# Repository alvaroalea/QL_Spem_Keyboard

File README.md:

# QL_Spem_Keyboard

Recreation of the mechanical keyboard for Sinclair QL computer by brand Spem

# WARNING: DO NOT USE THIS PROJECT IS NOT TESTED AND MISSING THINGS

Spem SRL, a italian company manufacture in 1986 a conversion kit for the Sinclair QL, named "System 2",
This include a aluminium desktop case with space for up to two 3 1/2" drives, the QL original Power supply and a Sinclair QL main board, to create a complete moderm desktop computer.

The case also incorporate a backplane where you can install a memory expansion and a disk interface.

The System 2 come with a full mechanical Keyboard, including numeric keys and 10 function keys, Spem use a unique aproach, and instead to provida a normal PC keyboard with a DIN-5 conector, design a specific one that connect directly to the keyboard conectors of the original Sinclair QL, and provide the aditional keys.

This is easy identificable because of the 20 cores ribbon cable the go from the keyboard to the case.

This project try to recreate this keyboard as identical as possible.
 
# Technical Details

The keyboard use keyswitch from Japanesse brand Futaba, referene MA-41 "Tombstone" because the top of the key is similar a tomb stone, with a cross emboss in the middle, while today's tipical keyswitchs the cross raise over the key.

This keyswitch has 3 legs, 2 of they are probably internally conected, to facilitate the develop of matrix keyboards using only 1 side of the PCB.

The combinations of keys need for some keys, like the F-5 F-10 that are really F1 to F5 at same time that shift keys, are from a pair of IC of type 4066, that are integrated analog swites, to power this 2 ic a small circuit drain the power from the keyboards lines itself.

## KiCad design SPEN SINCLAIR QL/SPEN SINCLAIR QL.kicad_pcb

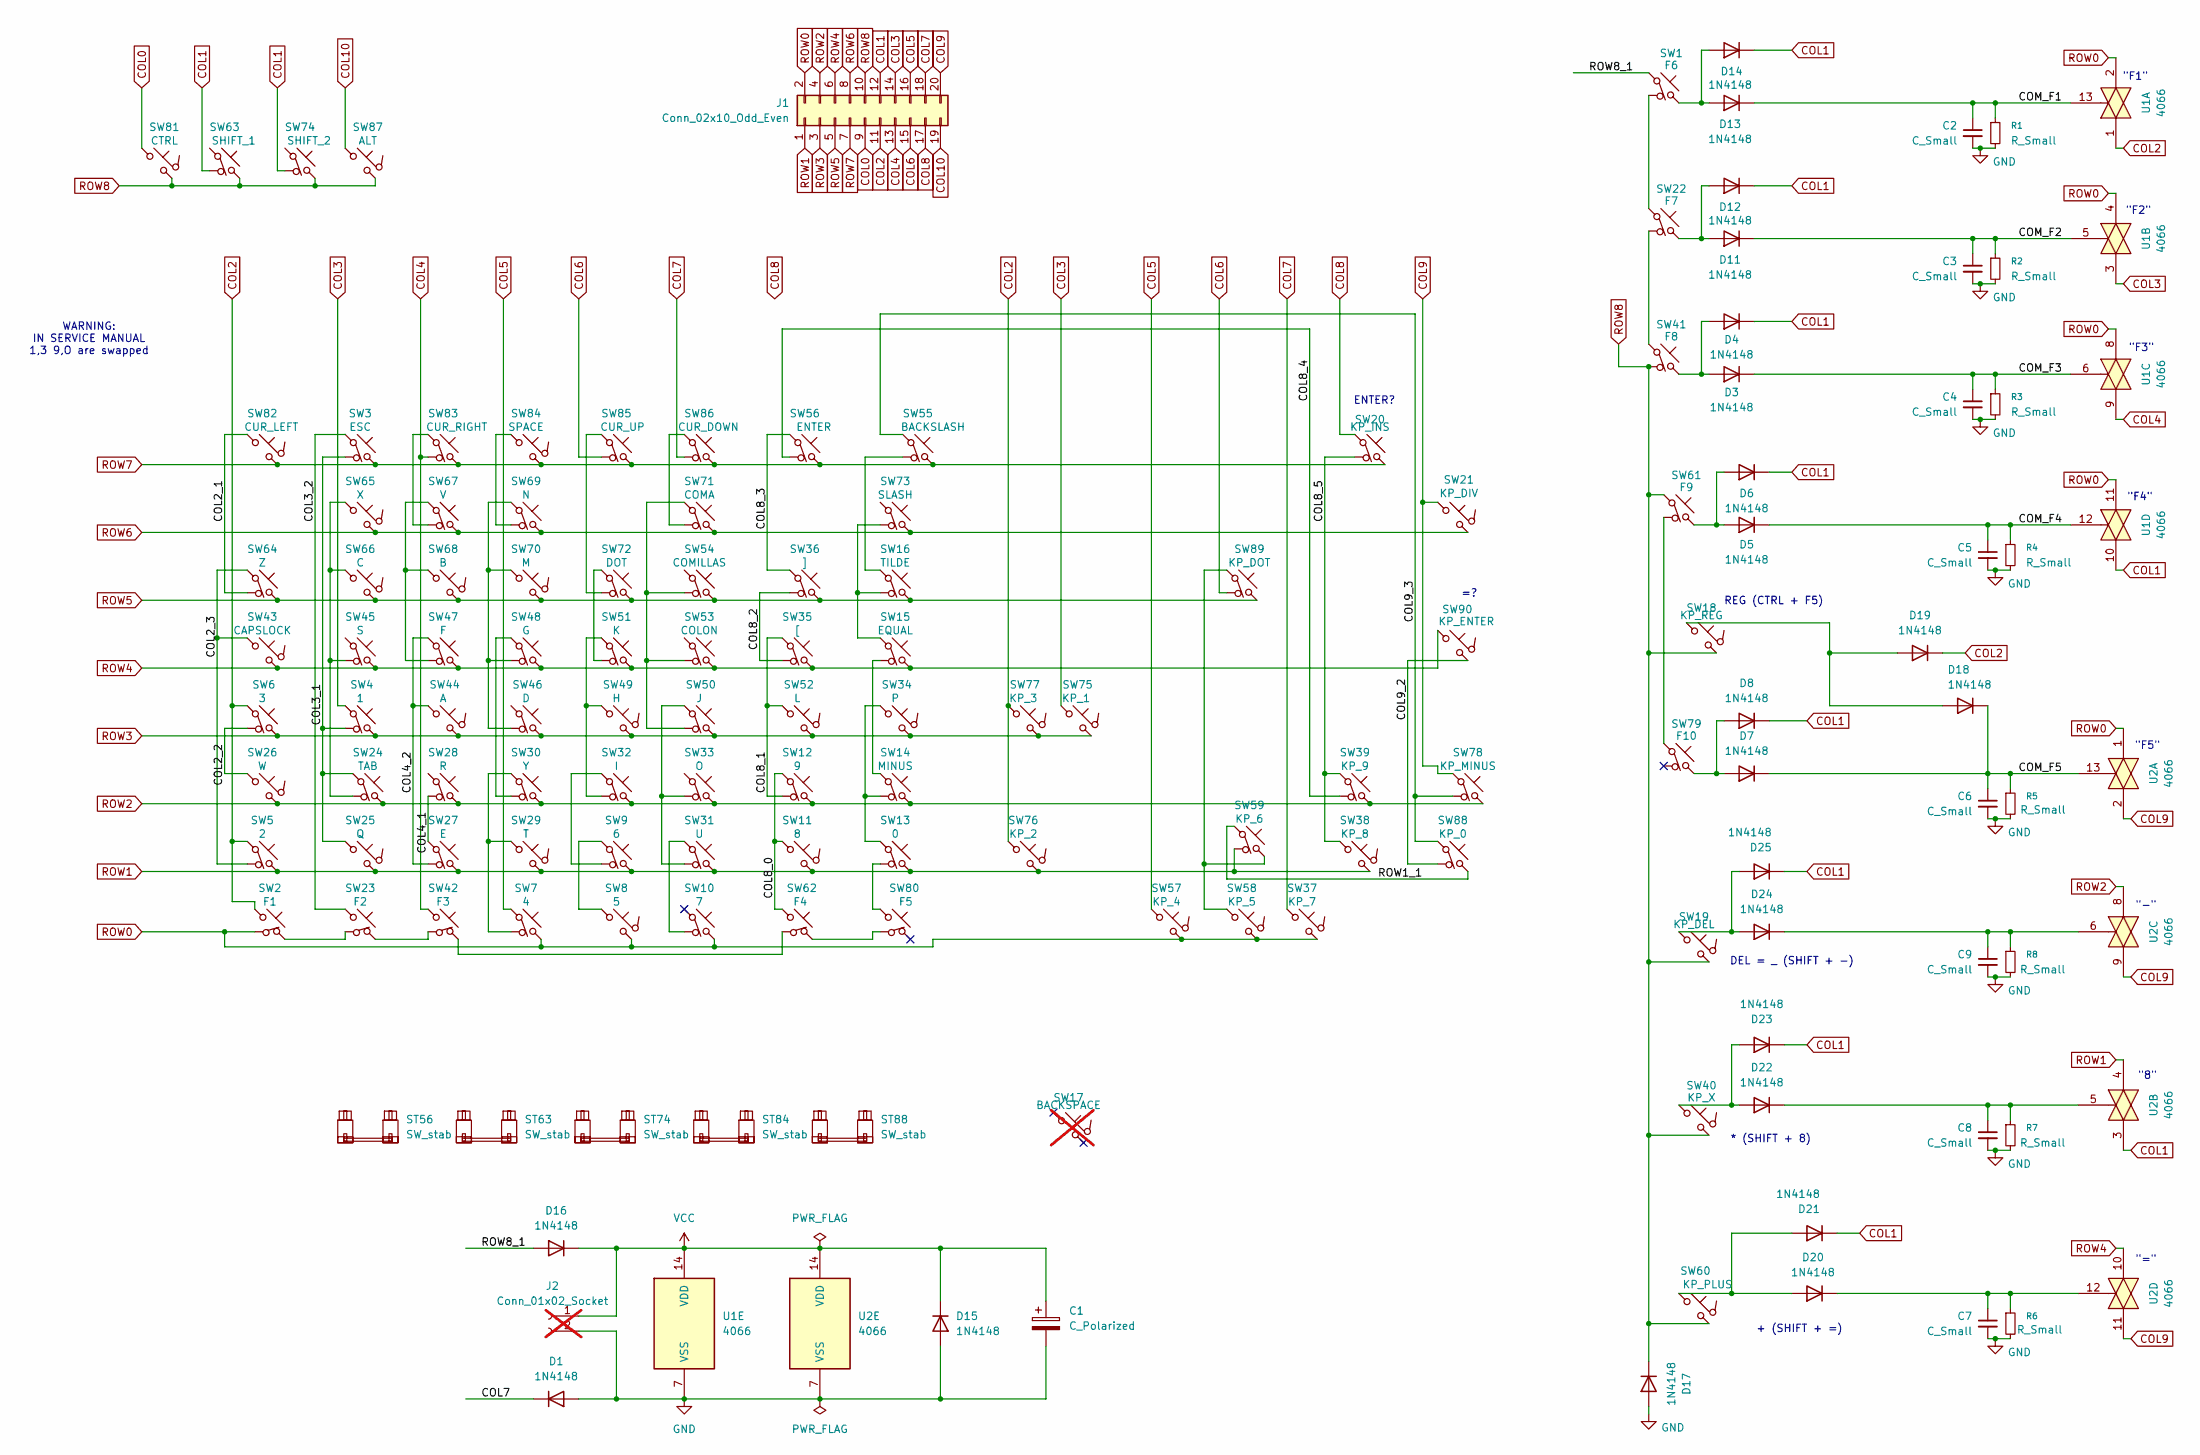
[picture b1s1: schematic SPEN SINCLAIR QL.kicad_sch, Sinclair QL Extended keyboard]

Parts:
C1: C_Polarized; C_Axial_L3.8mm_D2.6mm_P12.50mm_Horizontal
C2, C3, C4, C5, C6, C7, C8, C9: C_Small; C_Axial_DIN0207_L6.3mm_D2.5mm_P14.73mm_Horizontal
D1, D3, D4, D5, D6, D7, D8, D11, D12, D13, D14, D16, D18, D19, D20, D21, D22, D23, D24, D25: 1N4148; D_DO-35_SOD27_P10.16mm_Horizontal
D15: 1N4148; D_DO-35_SOD27_P12.70mm_Horizontal
D17: 1N4148; D_DO-35_SOD27_P7.62mm_Horizontal
J1: Conn_02x10_Odd_Even; PinHeader_2x10_P2.54mm_Horizontal
J2: Conn_01x02_Socket; PinHeader_1x02_P2.54mm_Horizontal; not fitted
R1, R2, R3, R4, R5, R6, R7, R8: R_Small; R_Axial_DIN0207_L6.3mm_D2.5mm_P14.73mm_Horizontal
ST56, ST63, ST74, ST88: SW_stab; Stabilizer_Cherry_MX_2.00u
ST84: SW_stab; Stabilizer_Cherry_MX_8.00u
SW1: F6; SW_Futaba_MA_PCB_1.00u
SW2: F1; SW_Futaba_MA_PCB_1.00u
SW3: ESC; SW_Futaba_MA_PCB_1.00u
SW4: 1; SW_Futaba_MA_PCB_1.00u
SW5: 2; SW_Futaba_MA_PCB_1.00u
SW6: 3; SW_Futaba_MA_PCB_1.00u
SW7: 4; SW_Futaba_MA_PCB_1.00u
SW8: 5; SW_Futaba_MA_PCB_1.00u
SW9: 6; SW_Futaba_MA_PCB_1.00u
SW10: 7; SW_Futaba_MA_PCB_1.00u
SW11: 8; SW_Futaba_MA_PCB_1.00u
SW12: 9; SW_Futaba_MA_PCB_1.00u
SW13: 0; SW_Futaba_MA_PCB_1.00u
SW14: MINUS; SW_Futaba_MA_PCB_1.00u
SW15: EQUAL; SW_Futaba_MA_PCB_1.00u
SW16: TILDE; SW_Futaba_MA_PCB_1.00u
SW17: BACKSPACE; SW_Futaba_MA_PCB_1.00u; not fitted
SW18: KP_REG; SW_Futaba_MA_PCB_1.00u
SW19: KP_DEL; SW_Futaba_MA_PCB_1.00u
SW20: KP_INS; SW_Futaba_MA_PCB_1.00u
SW21: KP_DIV; SW_Futaba_MA_PCB_1.00u
SW22: F7; SW_Futaba_MA_PCB_1.00u
SW23: F2; SW_Futaba_MA_PCB_1.00u
SW24: TAB; SW_Futaba_MA_PCB_1.00u
SW25: Q; SW_Futaba_MA_PCB_1.00u
SW26: W; SW_Futaba_MA_PCB_1.00u
SW27: E; SW_Futaba_MA_PCB_1.00u
SW28: R; SW_Futaba_MA_PCB_1.00u
SW29: T; SW_Futaba_MA_PCB_1.00u
SW30: Y; SW_Futaba_MA_PCB_1.00u
SW31: U; SW_Futaba_MA_PCB_1.00u
SW32: I; SW_Futaba_MA_PCB_1.00u
SW33: O; SW_Futaba_MA_PCB_1.00u
SW34: P; SW_Futaba_MA_PCB_1.00u
SW35: [; SW_Futaba_MA_PCB_1.00u
SW36: ]; SW_Futaba_MA_PCB_1.00u
SW37: KP_7; SW_Futaba_MA_PCB_1.00u
SW38: KP_8; SW_Futaba_MA_PCB_1.00u
SW39: KP_9; SW_Futaba_MA_PCB_1.00u
SW40: KP_X; SW_Futaba_MA_PCB_1.00u
SW41: F8; SW_Futaba_MA_PCB_1.00u
SW42: F3; SW_Futaba_MA_PCB_1.00u
SW43: CAPSLOCK; SW_Futaba_MA_PCB_1.00u
SW44: A; SW_Futaba_MA_PCB_1.00u
SW45: S; SW_Futaba_MA_PCB_1.00u
SW46: D; SW_Futaba_MA_PCB_1.00u
SW47: F; SW_Futaba_MA_PCB_1.00u
SW48: G; SW_Futaba_MA_PCB_1.00u
SW49: H; SW_Futaba_MA_PCB_1.00u
SW50: J; SW_Futaba_MA_PCB_1.00u
SW51: K; SW_Futaba_MA_PCB_1.00u
SW52: L; SW_Futaba_MA_PCB_1.00u
SW53: COLON; SW_Futaba_MA_PCB_1.00u
SW54: COMILLAS; SW_Futaba_MA_PCB_1.00u
SW55: BACKSLASH; SW_Futaba_MA_PCB_1.00u
SW56: ENTER; SW_Futaba_MA_PCB_1.00u
SW57: KP_4; SW_Futaba_MA_PCB_1.00u
SW58: KP_5; SW_Futaba_MA_PCB_1.00u
SW59: KP_6; SW_Futaba_MA_PCB_1.00u
SW60: KP_PLUS; SW_Futaba_MA_PCB_1.00u
SW61: F9; SW_Futaba_MA_PCB_1.00u
SW62: F4; SW_Futaba_MA_PCB_1.00u
SW63: SHIFT_1; SW_Futaba_MA_PCB_1.00u
SW64: Z; SW_Futaba_MA_PCB_1.00u
SW65: X; SW_Futaba_MA_PCB_1.00u
SW66: C; SW_Futaba_MA_PCB_1.00u
SW67: V; SW_Futaba_MA_PCB_1.00u
SW68: B; SW_Futaba_MA_PCB_1.00u
SW69: N; SW_Futaba_MA_PCB_1.00u
SW70: M; SW_Futaba_MA_PCB_1.00u
SW71: COMA; SW_Futaba_MA_PCB_1.00u
SW72: DOT; SW_Futaba_MA_PCB_1.00u
SW73: SLASH; SW_Futaba_MA_PCB_1.00u
SW74: SHIFT_2; SW_Futaba_MA_PCB_1.00u
SW75: KP_1; SW_Futaba_MA_PCB_1.00u
SW76: KP_2; SW_Futaba_MA_PCB_1.00u
SW77: KP_3; SW_Futaba_MA_PCB_1.00u
SW78: KP_MINUS; SW_Futaba_MA_PCB_1.00u
SW79: F10; SW_Futaba_MA_PCB_1.00u
SW80: F5; SW_Futaba_MA_PCB_1.00u
SW81: CTRL; SW_Futaba_MA_PCB_1.00u
SW82: CUR_LEFT; SW_Futaba_MA_PCB_1.00u
SW83: CUR_RIGHT; SW_Futaba_MA_PCB_1.00u
SW84: SPACE; SW_Futaba_MA_PCB_1.00u
SW85: CUR_UP; SW_Futaba_MA_PCB_1.00u
SW86: CUR_DOWN; SW_Futaba_MA_PCB_1.00u
SW87: ALT; SW_Futaba_MA_PCB_1.00u
SW88: KP_0; SW_Futaba_MA_PCB_1.00u
SW89: KP_DOT; SW_Futaba_MA_PCB_1.00u
SW90: KP_ENTER; SW_Futaba_MA_PCB_1.00u
U1, U2: 4066; DIP-14_W7.62mm_LongPads

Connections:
/COL2_1: SW64.3, SW82.1
/COL2_2: SW6.3, SW26.1
/COL2_3: SW5.3, SW43.1, SW64.1
/COL3_1: SW3.3, SW4.3, SW24.1, SW25.1
/COL3_2: SW3.1, SW23.2
/COL4_1: SW27.1, SW28.3
/COL4_2: SW27.3, SW44.1, SW47.1
/COL8_0: SW11.1, SW12.1, SW62.2
/COL8_1: SW12.3, SW35.1, SW52.1
/COL8_2: SW35.3, SW36.3
/COL8_3: SW36.1, SW56.1
/COL8_4: SW39.3, SW56.3
/COL8_5: SW20.3, SW38.1, SW39.1
/COL9_2: SW88.3, SW90.2
/COL9_3: SW55.1, SW78.3, SW88.1
/COM_F1: C2.1, D13.1 (K), R1.1, U1.13
/COM_F2: C3.1, D11.1 (K), R2.1, U1.5
/COM_F3: C4.1, D3.1 (K), R3.1, U1.6
/COM_F4: C5.1, D5.1 (K), R4.1, U1.12
/COM_F5: C6.1, D7.1 (K), D18.1 (K), R5.1, U2.13
/ROW1_1: SW59.1, SW88.2
/ROW8_1: D16.2 (A), SW1.1
COL0: J1.9, SW81.1
COL1: D4.1 (K), D6.1 (K), D8.1 (K), D12.1 (K), D14.1 (K), D21.1 (K), D23.1 (K), D25.1 (K), J1.12, SW63.3, SW74.3, U1.10, U2.3
COL2: D19.1 (K), J1.11, SW2.2, SW5.1, SW6.1, SW76.1, SW77.1, U1.1
COL3: J1.14, SW4.1, SW75.1, U1.3
COL4: J1.13, SW42.2, SW83.3, U1.9
COL5: J1.16, SW7.1, SW57.1
COL6: J1.15, SW85.3, SW89.3
COL7: D1.1 (K), J1.18, SW37.1, SW86.3
COL8: J1.17, SW20.1
COL9: J1.20, SW21.1, SW78.1, U2.2, U2.9, U2.11
COL10: J1.19, SW87.1
COM_8: C8.1, D22.1 (K), R7.1, U2.5
COM_MINUS: C9.1, D24.1 (K), R8.1, U2.6
COM_PLUS: C7.1, D20.1 (K), R6.1, U2.12
GND: C1.2, C2.2, C3.2, C4.2, C5.2, C6.2, C7.2, C8.2, C9.2, D1.2 (A), D15.2 (A), D17.2 (A), J2.2, R1.2, R2.2, R3.2, R4.2, R5.2, R6.2, R7.2, R8.2, U1.7 (VSS), U2.7 (VSS)
unnamed: D3.2 (A), D4.2 (A), SW41.2
unnamed: D5.2 (A), D6.2 (A), SW61.2
unnamed: D7.2 (A), D8.2 (A), SW79.2
unnamed: D11.2 (A), D12.2 (A), SW22.2
unnamed: D13.2 (A), D14.2 (A), SW1.2
unnamed: D18.2 (A), D19.2 (A), SW18.1
unnamed: D20.2 (A), D21.2 (A), SW60.1
unnamed: D22.2 (A), D23.2 (A), SW40.1
unnamed: D24.2 (A), D25.2 (A), SW19.1
unnamed: SW1.3, SW22.1
unnamed: SW2.3, SW23.1
unnamed: SW8.1, SW9.1
unnamed: SW10.3, SW31.1
unnamed: SW13.1, SW80.2
unnamed: SW13.3, SW14.3, SW34.1
unnamed: SW14.1, SW15.3
unnamed: SW15.1, SW16.3, SW73.3
unnamed: SW16.1, SW55.3
unnamed: SW22.3, SW41.1
unnamed: SW23.3, SW42.1
unnamed: SW24.3, SW45.3, SW65.1, SW66.1
unnamed: SW7.3, SW29.1, SW30.1
unnamed: SW30.3, SW48.1
unnamed: SW31.3, SW33.3, SW50.1
unnamed: SW9.3, SW32.1
unnamed: SW32.3, SW49.1, SW51.1
unnamed: SW42.3, SW62.1
unnamed: SW46.3, SW48.3, SW69.1, SW70.1
unnamed: SW47.3, SW67.1, SW68.1
unnamed: SW50.3, SW53.3, SW54.3, SW71.1
unnamed: SW51.3, SW72.1
unnamed: SW58.1, SW59.2, SW89.1
unnamed: SW61.3, SW79.1
unnamed: SW62.3, SW80.1
unnamed: SW67.3, SW83.1
unnamed: SW69.3, SW84.1
unnamed: SW71.3, SW86.1
unnamed: SW72.3, SW85.1
ROW0: J1.2, SW2.1, SW7.2, SW8.2, SW10.2, SW37.2, SW57.2, SW58.2, U1.2, U1.4, U1.8, U1.11, U2.1
ROW1: J1.1, SW5.2, SW9.2, SW11.2, SW13.2, SW25.2, SW27.2, SW29.2, SW31.2, SW38.2, SW59.3, SW76.2, U2.4
ROW2: J1.4, SW12.2, SW14.2, SW24.2, SW26.2, SW28.2, SW30.2, SW32.2, SW33.2, SW39.2, SW78.2, U2.8
ROW3: J1.3, SW4.2, SW6.2, SW34.2, SW44.2, SW46.2, SW49.2, SW50.2, SW52.2, SW75.2, SW77.2
ROW4: J1.6, SW15.2, SW35.2, SW43.2, SW45.2, SW47.2, SW48.2, SW51.2, SW53.2, SW90.1, U2.10
ROW5: J1.5, SW16.2, SW36.2, SW54.2, SW64.2, SW66.2, SW68.2, SW70.2, SW72.2, SW89.2
ROW6: J1.8, SW21.2, SW65.2, SW67.2, SW69.2, SW71.2, SW73.2
ROW7: J1.7, SW3.2, SW20.2, SW55.2, SW56.2, SW82.2, SW83.2, SW84.2, SW85.2, SW86.2
ROW8: D17.1 (K), J1.10, SW18.2, SW19.2, SW40.2, SW41.3, SW60.2, SW61.1, SW63.2, SW74.2, SW81.2, SW87.2
VCC: C1.1, D15.1 (K), D16.1 (K), J2.1, U1.14 (VDD), U2.14 (VDD)

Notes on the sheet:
DEL = _ (SHIFT + -)
ENTER?
"F2"
"8"
"-"
"F3"
REG (CTRL + F5)
"="
WARNING: IN SERVICE MANUAL 1,3 9,O are swapped
"F5"
* (SHIFT + 8)
"F4"
+ (SHIFT + =)
"F1"

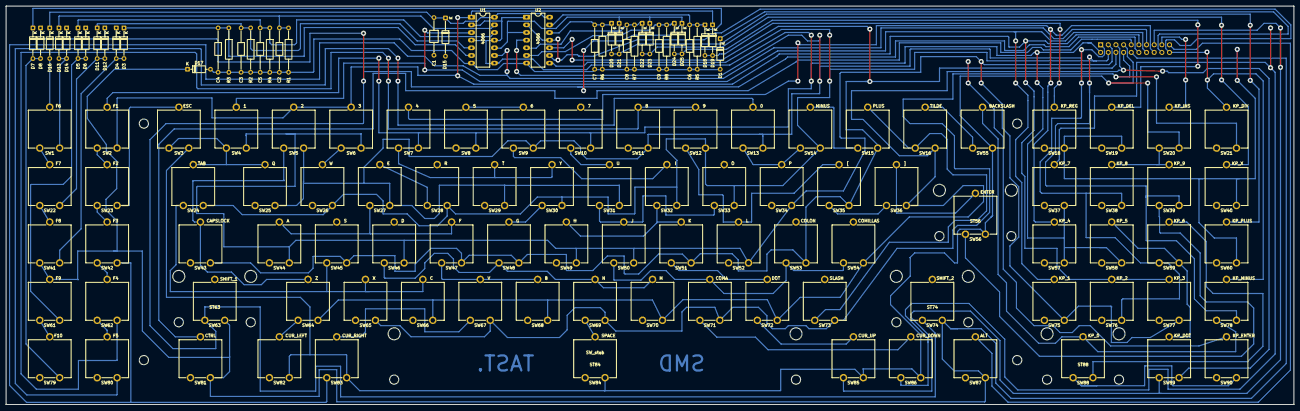
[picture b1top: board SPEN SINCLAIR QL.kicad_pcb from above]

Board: 2 copper layers, 427.4 x 132.2 mm, 136 parts (1 on the bottom side), 85 nets.

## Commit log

2026-05-29 initial
